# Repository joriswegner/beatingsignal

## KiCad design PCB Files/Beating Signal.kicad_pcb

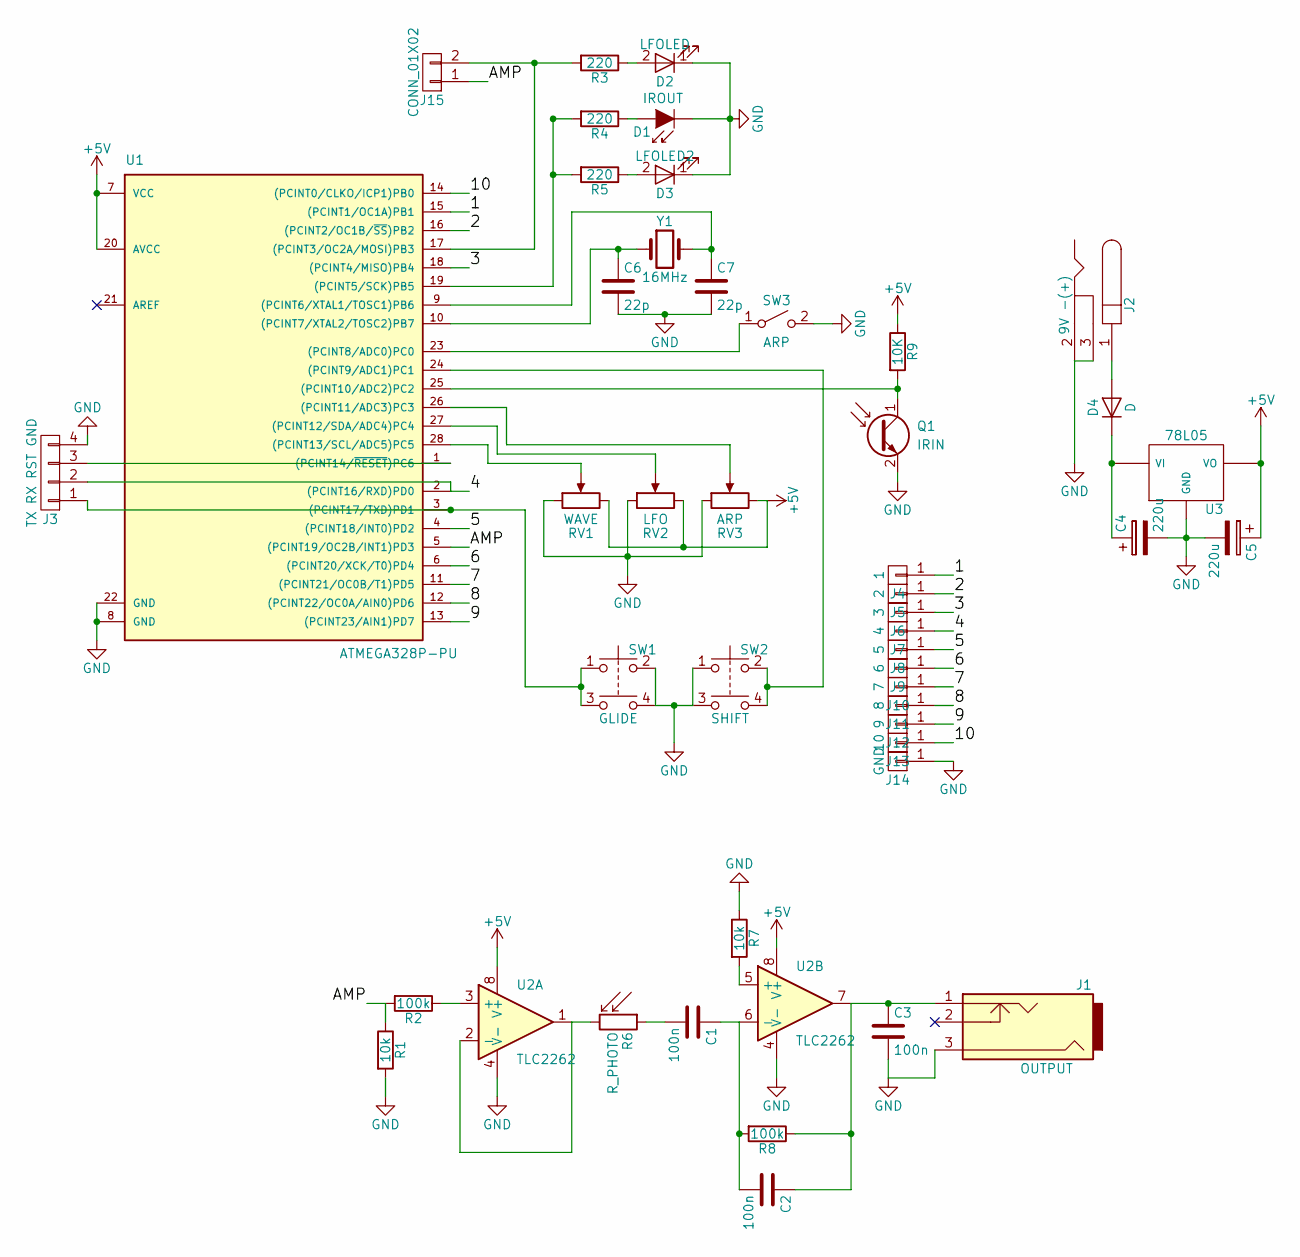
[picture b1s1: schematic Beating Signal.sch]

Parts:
C1, C2, C3: 100n; C_Rect_L7.0mm_W2.5mm_P5.00mm
C4, C5: 220u; CP_Radial_D5.0mm_P2.50mm
C6, C7: 22p; C_Disc_D3.0mm_W1.6mm_P2.50mm
D1: IROUT; LED_SideEmitter_Rectangular_W4.5mm_H1.6mm
D2: LFOLED; LED_D5.0mm
D3: LFOLED2; LED_D5.0mm
D4: D; D_DO-41_SOD81_P7.62mm_Horizontal
J1: OUTPUT; Buchse
J2: 9V -(+); BARREL_JACK
J3: TX RX RST GND; Pin_Header_Straight_1x04_Pitch2.54mm
J4: 1; Cross_Contact_A02
J5: 2; Cross_Contact_A02
J6: 3; Cross_Contact_A02
J7: 4; Cross_Contact_A02
J8: 5; Cross_Contact_A02
J9: 6; Cross_Contact_A02
J10: 7; Cross_Contact_A02
J11: 8; Cross_Contact_A02
J12: 9; Cross_Contact_A02
J13: 10; BeatingSignalNameA02
J14: GND; GND_Contact_A01
J15: CONN_01X02; Pin_Header_Straight_1x02_Pitch2.54mm
Q1: IRIN; LED_D5.0mm
R1, R7: 10k; R_Axial_DIN0207_L6.3mm_D2.5mm_P7.62mm_Horizontal
R2, R8: 100k; R_Axial_DIN0207_L6.3mm_D2.5mm_P7.62mm_Horizontal
R3, R4, R5: 220; R_Axial_DIN0207_L6.3mm_D2.5mm_P7.62mm_Horizontal
R6: R_PHOTO; LED_D5.0mm
R9: 10K; R_Axial_DIN0207_L6.3mm_D2.5mm_P7.62mm_Horizontal
RV1: WAVE; Potentiometer_Alps_RK09K_Vertical
RV2: LFO; Potentiometer_Alps_RK09K_Vertical
RV3: ARP; Potentiometer_Alps_RK09K_Vertical
SW1: GLIDE; Switch_DT6SW
SW2: SHIFT; Switch_DT6SW
SW3: ARP; Switch_DT6SW
U1: ATMEGA328P-PU; DIP-28_W7.62mm
U2: TLC2262; DIP-8_W7.62mm
U3: 78L05; 78L05_TO-92
Y1: 16MHz; Crystal_HC49-4H_Vertical

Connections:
+5V: C5.1, R9.1, RV1.3, RV2.3, RV3.3, U1.7 (VCC), U1.20 (AVCC), U2.8 (V+), U3.VO
/1: J4.1, U1.15 ((PCINT1/OC1A)PB1)
/2: J5.1, U1.16 ((PCINT2/OC1B/~SS~)PB2)
/3: J6.1, U1.18 ((PCINT4/MISO)PB4)
/4: J3.2, J7.1, U1.2 ((PCINT16/RXD)PD0)
/5: J8.1, U1.4 ((PCINT18/INT0)PD2)
/6: J9.1, U1.6 ((PCINT20/XCK/T0)PD4)
/7: J10.1, U1.11 ((PCINT21/OC0B/T1)PD5)
/8: J11.1, U1.12 ((PCINT22/OC0A/AIN0)PD6)
/9: J12.1, U1.13 ((PCINT23/AIN1)PD7)
/10: J13.1, U1.14 ((PCINT0/CLKO/ICP1)PB0)
/AMP: J15.1, R1.1, R2.2, U1.5 ((PCINT19/OC2B/INT1)PD3)
GND: C3.2, C4.2, C5.2, C6.2, C7.2, D1.1 (K), D2.1 (K), D3.1 (K), J1.3, J2.2, J2.3, J3.4, J14.1, Q1.2 (E), R1.2, R7.1, RV1.1, RV2.1, RV3.1, SW1.2, SW1.4, SW2.1, SW2.3, SW3.2 (B), U1.8 (GND), U1.22 (GND), U2.4 (V-), U3.GND
unnamed: C1.1, C2.2, R8.2, U2.6 (-)
unnamed: C1.2, R6.1
unnamed: C2.1, C3.1, J1.1, R8.1, U2.7
unnamed: C4.1, D4.1 (K), U3.VI
unnamed: C6.1, U1.10 ((PCINT7/XTAL2/TOSC2)PB7), Y1.1
unnamed: C7.1, U1.9 ((PCINT6/XTAL1/TOSC1)PB6), Y1.2
unnamed: D1.2 (A), R4.1
unnamed: D2.2 (A), R3.1
unnamed: D3.2 (A), R5.1
unnamed: D4.2 (A), J2.1
unnamed: J3.1, SW1.1, SW1.3, U1.3 ((PCINT17/TXD)PD1)
unnamed: J3.3, U1.1 ((PCINT14/~RESET~)PC6)
unnamed: J15.2, R3.2, U1.17 ((PCINT3/OC2A/MOSI)PB3)
unnamed: Q1.1 (C), R9.2, U1.25 ((PCINT10/ADC2)PC2)
unnamed: R2.1, U2.3 (+)
unnamed: R4.2, R5.2, U1.19 ((PCINT5/SCK)PB5)
unnamed: R6.2, U2.1, U2.2 (-)
unnamed: R7.2, U2.5 (+)
unnamed: RV1.2, U1.28 ((PCINT13/SCL/ADC5)PC5)
unnamed: RV2.2, U1.27 ((PCINT12/SDA/ADC4)PC4)
unnamed: RV3.2, U1.26 ((PCINT11/ADC3)PC3)
unnamed: SW2.2, SW2.4, U1.24 ((PCINT9/ADC1)PC1)
unnamed: SW3.1 (A), U1.23 ((PCINT8/ADC0)PC0)

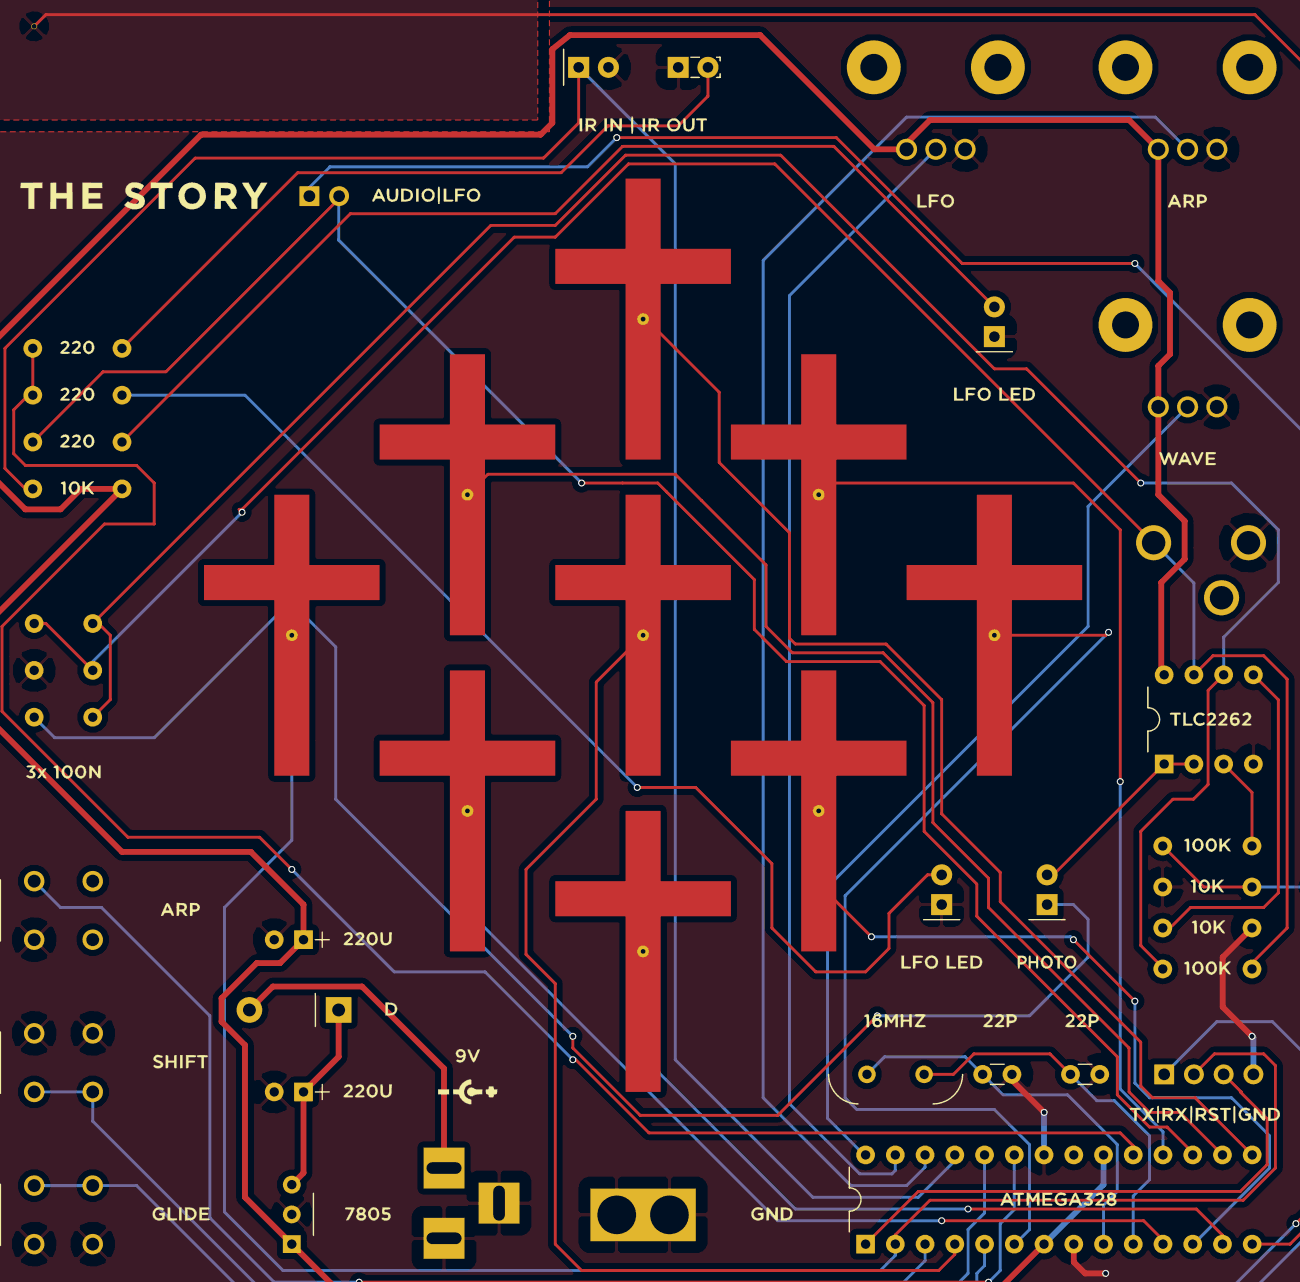
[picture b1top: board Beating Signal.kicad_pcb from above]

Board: 2 copper layers, 46 parts (0 on the bottom side), 36 nets.

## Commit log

2018-04-08 Beating Signal - The Story 1.0
    Arduino-Code, Bauanleitung und Daten des Kicad-Projektes für Beating Signals Cover-Synthesizer.
